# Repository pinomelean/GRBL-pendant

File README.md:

# GRBL-pendant

Hardware pendant intended for use with G-code senders for GRBL machines

### Description
The aim of this project is to produce a physical controller which functions similarly to a machine pendant, but is not limited to only that. The device would allow the user to interact with both the computer and the CNC machine without needing to reach for the mouse and keyboard for the most machining tasks.
The hardware is not limited to a single purpose, though, as the firmware can be easily changed so the controller can suit the needs of the user, and be adapted for their particular workflow.

This USB pendant Includes many buttons, encoders and a thumbstick that can be configured with the most common functions and G-code commands you need to use your machine.
It uses a Teensy++ 2 because of its physical size, IO, native USB, and ease of programming with the Arduino ecosystem, *as limited as it is*.

### Free and open source

I publish all the files necessary for anyone to "DIY" it, all files can be opened and edited with FOSS software.
Anyone with a CNC mill/router should be able to make their own if they're so inclined.

The code is written as simple as I can manage (even if I suck at it), so anyone with basic knowledge and/or an Arduino tutorial open in another tab can modify it to suit their needs.

The PCBs are designed in KiCad and made to be simple enough to be milled at home, as I've done with the first prototype.

To mill the PCBs I used, and would recommend, [Juan Pablo Caram](https://github.com/jpcaram)'s [FlatCAM](http://www.flatcam.org/) and [Martin Pittermann](https://github.com/martin2250)'s [OpenCNCPilot](https://github.com/martin2250/OpenCNCPilot)

FreeCAD was used to design the silicone keypad and the mould to cast it.
The mould and the case were milled using toolpaths generated in the path workbench.

## Pendant layout

The layout I had in mind designing this pendant, and will come by default will be the following:

The Thumbstick is used either as a mouse pointer, along with a couple of buttons for clicking, or to quickly jog the machine when pressed in.

*The Teensy can emulate a game controller thumbstick, but as not many G-code sender applications support game controllers, and those that do (I only tested UGS) may not recognize the one emulated by the teensy, the thumbstick will not be emulating a game controller for nw, and just write G-code jog commands instead. This should work with any sender.*

The buttons at the top of the pendant are dedicated to the basic machine commands: Reset, Feed hold, Cycle start/Resume at the top, and Home machine and Kill alarm lock right of the thumbstick.

There are three encoders for fine jogging of each axis. By default each detent should result in 1mm of travel, and 0.1mm if the encoder is pushed in while turning.
Pushing an encoder without turning it will zero that axis.

The two other encoders are meant for Feed and spindle speed overrides, but could be used for jogging two extra axises in a 5-axis machine if anyone's running one of those.

*I still need to figure how to send the Feed and Spindle speed override command characters through a sender application if it does not have hotkeys for that*

Next to each encoder is a button which is used to individually home that axis.
For the Feed and Spindle encoders, the button resets it to 100%.

At the bottom of the controller are the macro buttons.
The five ones in the middle are used for probing or touching against a workpiece from every direction (except from under it).

The other 4 buttons are left for any extra macros the user could need, such as turning on/off mist/flood coolant, starting/stopping the spindle, touching a bit on the tool setter...

**Of course, all of the actions are remappable and configurable to suit the needs and workflow of the user. The defaults are just what** ***I*** **think is most useful**

## Project status

- Second version built. Looks much nicer in black and white. Probably final version if no issues arise.
	- The keypad also feels nice and works very well, but the Shore A20 durometer silicone might be too soft for this application, but will do for mow.

- Keypad mould machined. Couldn't get the 3D surfacing operation to work with a ball end mill en FreeCAD, so I had to resort to Fusion360 for that operation.
	- A sprue and vent have to be drilled manually into the side to inject the silicone with a syringe and push out the air.

- First prototype mostly built, silicone keypad left to see how it all looks and feels. A couple of encoder push buttons don't work, but will do for testing.
	- Several adjustments made for a second version. Will not make a mold and keypad for the first.

- Thumbstick as mouse pointer - Done. Works pretty well in the smaller screens I use, slower in bigger ones, but it's adjustable.
- Thumbstick for jogging - UGS wouldn't recognize it in game controller mode, so It just types jogging G-code commands. Works ok.
- Encoder jogging - Works well for accurate positioning. Too slow for jogging around a bigger machine, but there's the thumbstick for that.
- Rest of the buttons - not yet programmed.

## Notes

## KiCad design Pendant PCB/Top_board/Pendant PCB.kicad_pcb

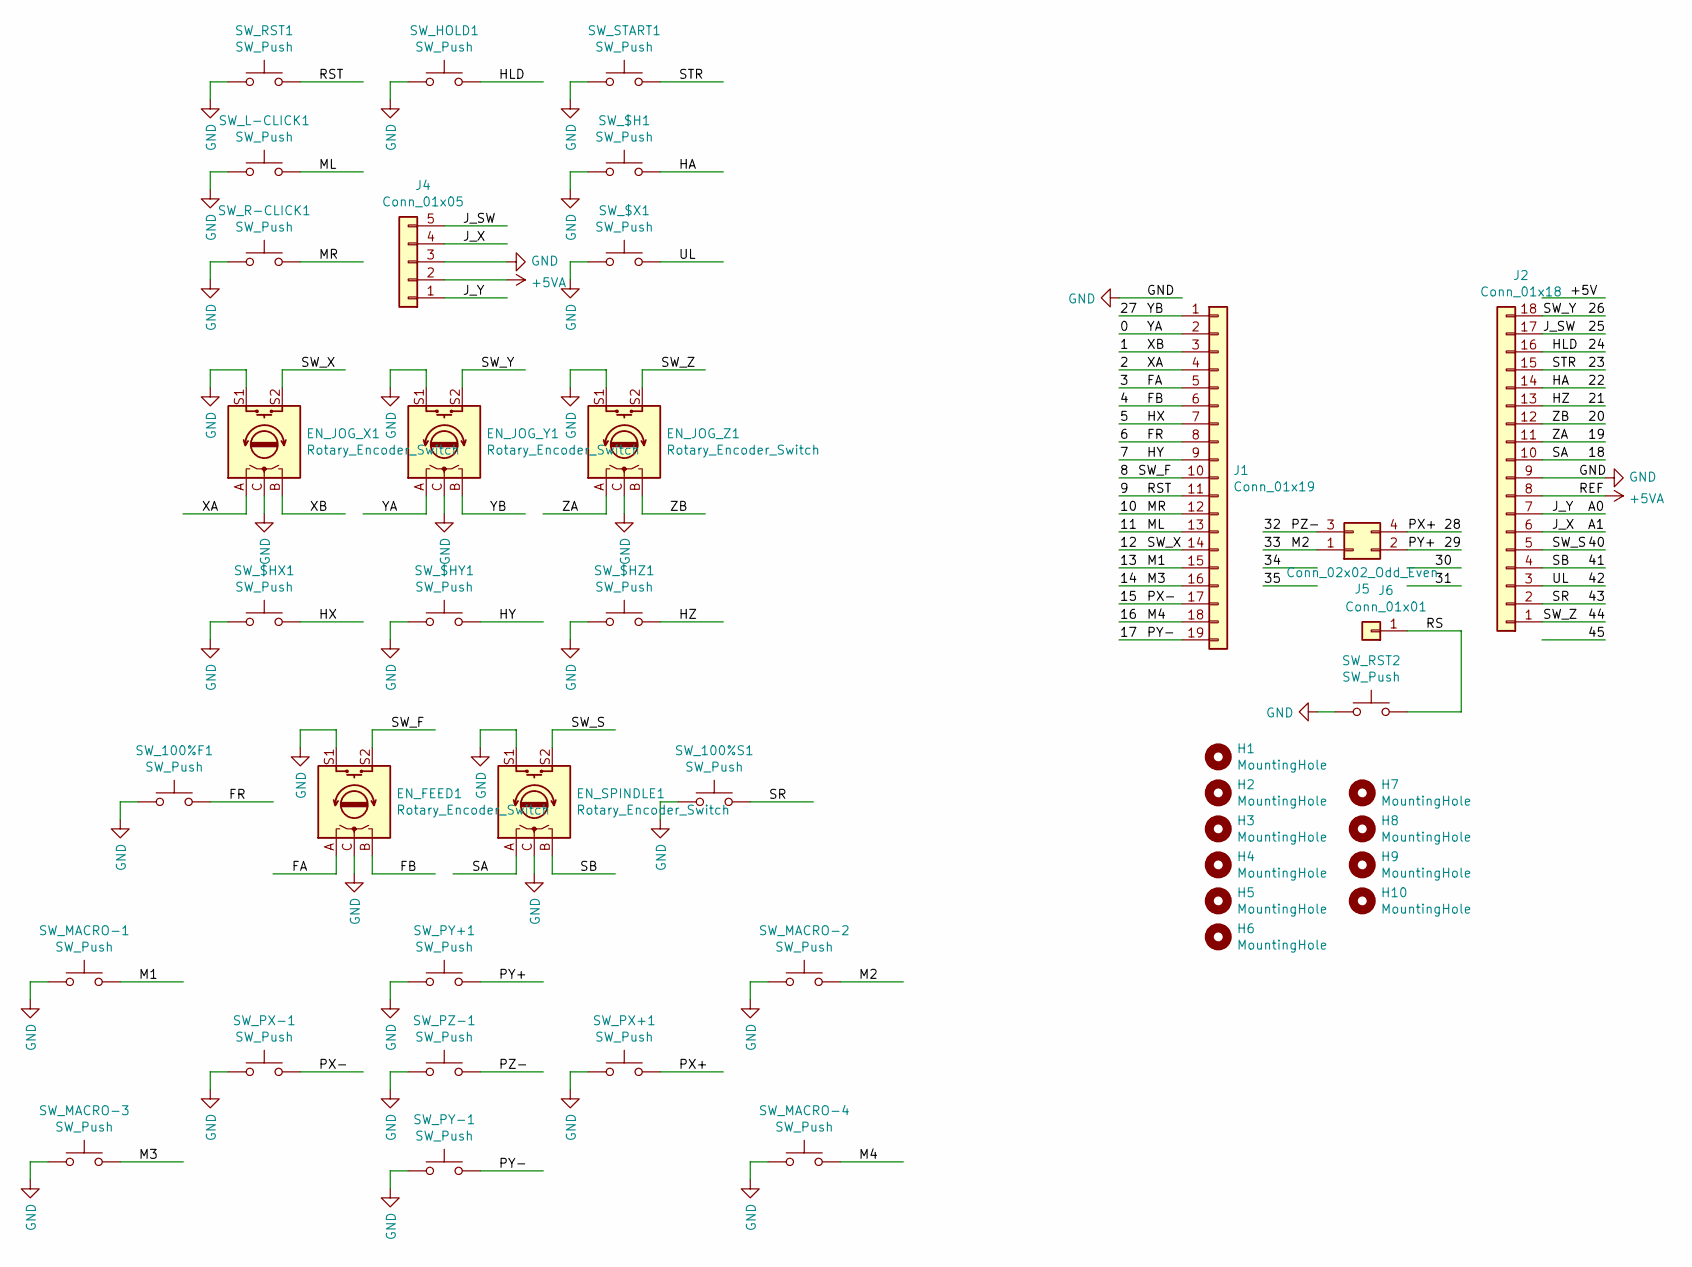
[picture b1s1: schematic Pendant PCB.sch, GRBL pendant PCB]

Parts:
EN_FEED1: Rotary_Encoder_Switch; PEC11R-4x15K
EN_JOG_X1: Rotary_Encoder_Switch; PEC11R-4x15K
EN_JOG_Y1: Rotary_Encoder_Switch; PEC11R-4x15K
EN_JOG_Z1: Rotary_Encoder_Switch; PEC11R-4x15K
EN_SPINDLE1: Rotary_Encoder_Switch; PEC11R-4x15K
H1, H2, H3, H4, H5, H6: MountingHole; MountingHole_2.5mm
H7, H8, H9, H10: MountingHole; MountingHole_3.2mm_M3
J1: Conn_01x19; PinHeader_1x19_P2.54mm_Vertical
J2: Conn_01x18; PinHeader_1x18_P2.54mm_Vertical
J4: Conn_01x05; PinHeader_1x05_P2.54mm_Vertical
J5: Conn_02x02_Odd_Even; PinHeader_2x02_P2.54mm_Vertical
J6: Conn_01x01; PinHeader_1x01_P2.54mm_Vertical
SW_100%F1, SW_100%S1: SW_Push; SW_PUSH_6mm_H7.3mm
SW_$H1: SW_Push; SW_PUSH_6mm_H7.3mm
SW_$HX1: SW_Push; SW_PUSH_6mm_H7.3mm
SW_$HY1: SW_Push; SW_PUSH_6mm_H7.3mm
SW_$HZ1: SW_Push; SW_PUSH_6mm_H7.3mm
SW_$X1: SW_Push; SW_PUSH_6mm_H7.3mm
SW_HOLD1: SW_Push; SW_PUSH_6mm_H7.3mm
SW_L-CLICK1: SW_Push; SW_PUSH_6mm_H7.3mm
SW_MACRO-1, SW_MACRO-2, SW_MACRO-3, SW_MACRO-4: SW_Push; SW_PUSH_6mm_H7.3mm
SW_PX+1: SW_Push; SW_PUSH_6mm_H7.3mm
SW_PX-1: SW_Push; SW_PUSH_6mm_H7.3mm
SW_PY+1: SW_Push; SW_PUSH_6mm_H7.3mm
SW_PY-1: SW_Push; SW_PUSH_6mm_H7.3mm
SW_PZ-1: SW_Push; SW_PUSH_6mm_H7.3mm
SW_R-CLICK1: SW_Push; SW_PUSH_6mm_H7.3mm
SW_RST1: SW_Push; SW_PUSH_6mm_H7.3mm
SW_RST2: SW_Push; SW_Tactile_SPST_Angled_PTS645Vx39-2LFS
SW_START1: SW_Push; SW_PUSH_6mm_H7.3mm

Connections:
+5VA: J2.8, J4.2
/0: EN_JOG_Y1.A, J1.2
/1: EN_JOG_X1.B, J1.3
/2: EN_JOG_X1.A, J1.4
/3: EN_FEED1.A, J1.5
/4: EN_FEED1.B, J1.6
/5: J1.7, SW_$HX1.2
/6: J1.8, SW_100%F1.2
/7: J1.9, SW_$HY1.2
/8: EN_FEED1.S2, J1.10
/9: J1.11, SW_RST1.1
/10: J1.12, SW_R-CLICK1.1
/11: J1.13, SW_L-CLICK1.1
/12: EN_JOG_X1.S2, J1.14
/13: J1.15, SW_MACRO-1.2
/14: J1.16, SW_MACRO-3.2
/15: J1.17, SW_PX-1.1
/16: J1.18, SW_MACRO-4.1
/17: J1.19, SW_PY-1.1
/18: EN_SPINDLE1.A, J2.10
/19: EN_JOG_Z1.A, J2.11
/20: EN_JOG_Z1.B, J2.12
/21: J2.13, SW_$HZ1.2
/22: J2.14, SW_$H1.1
/23: J2.15, SW_START1.1
/24: J2.16, SW_HOLD1.2
/25: J2.17, J4.5
/26: EN_JOG_Y1.S2, J2.18
/27: EN_JOG_Y1.B, J1.1
/28: J5.4, SW_PX+1.1
/29: J5.2, SW_PY+1.2
/32: J5.3, SW_PZ-1.1
/33: J5.1, SW_MACRO-2.1
/40: EN_SPINDLE1.S2, J2.5
/41: EN_SPINDLE1.B, J2.4
/42: J2.3, SW_$X1.1
/43: J2.2, SW_100%S1.2
/44: EN_JOG_Z1.S2, J2.1
/A0: J2.7, J4.1
/A1: J2.6, J4.4
/RS: J6.1, SW_RST2.2
GND: EN_FEED1.C, EN_FEED1.S1, EN_JOG_X1.C, EN_JOG_X1.S1, EN_JOG_Y1.C, EN_JOG_Y1.S1, EN_JOG_Z1.C, EN_JOG_Z1.S1, EN_SPINDLE1.C, EN_SPINDLE1.S1, J2.9, J4.3, SW_100%F1.1, SW_100%S1.1, SW_$H1.2, SW_$HX1.1, SW_$HY1.1, SW_$HZ1.1, SW_$X1.2, SW_HOLD1.1, SW_L-CLICK1.2, SW_MACRO-1.1, SW_MACRO-2.2, SW_MACRO-3.1, SW_MACRO-4.2, SW_PX+1.2, SW_PX-1.2, SW_PY+1.1, SW_PY-1.2, SW_PZ-1.2, SW_R-CLICK1.2, SW_RST1.2, SW_RST2.1, SW_START1.2

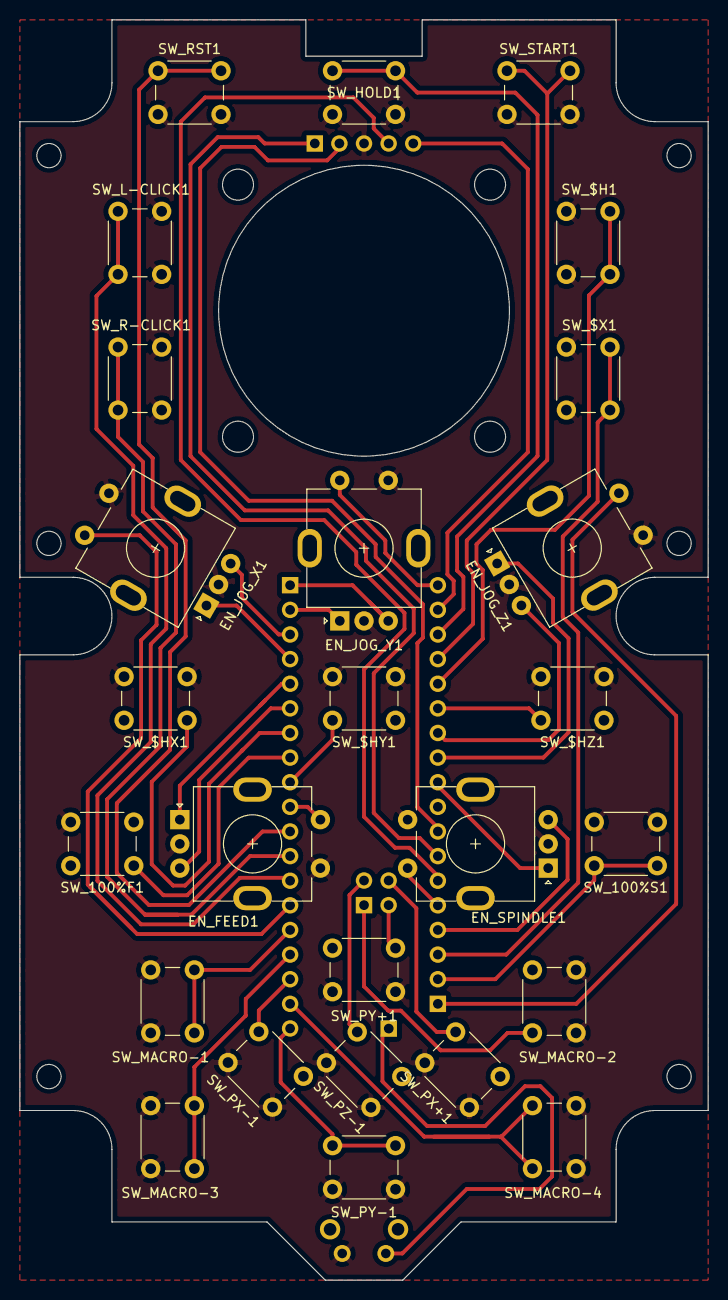
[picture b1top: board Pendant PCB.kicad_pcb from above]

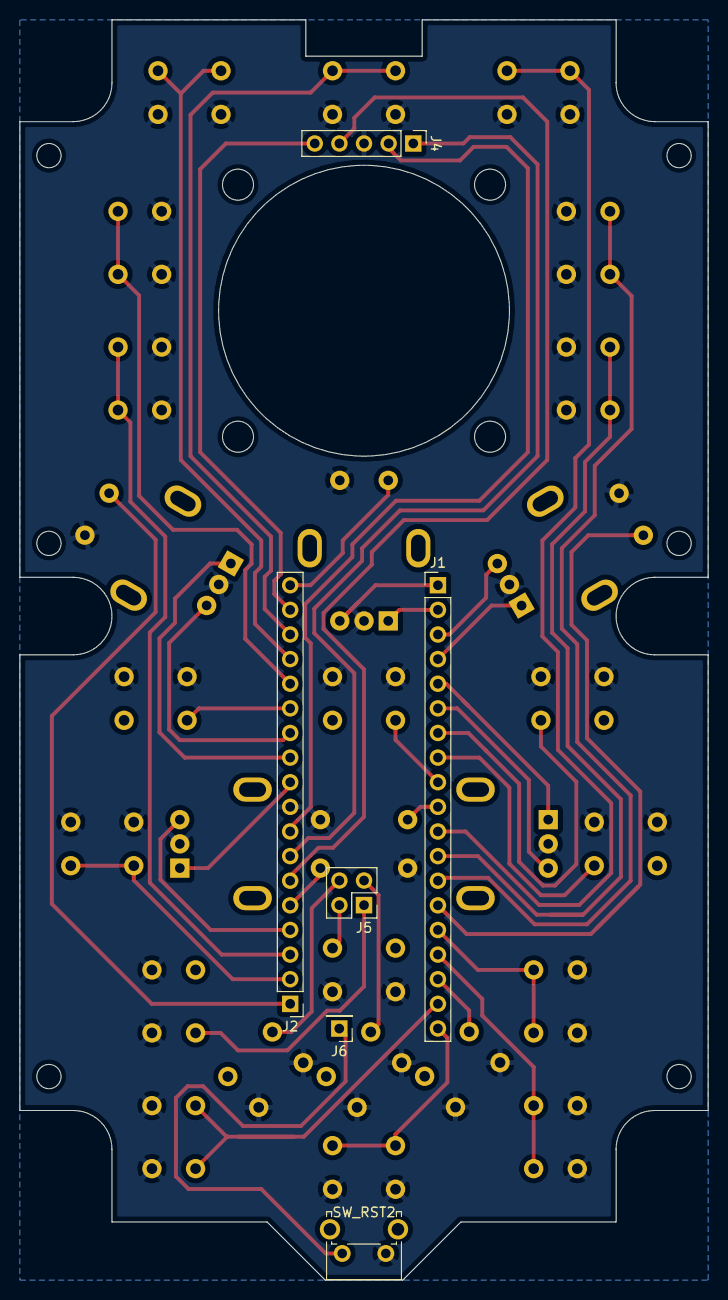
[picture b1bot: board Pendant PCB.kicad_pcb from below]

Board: 2 copper layers, 71.0 x 130.0 mm, 42 parts (6 on the bottom side), 42 nets.

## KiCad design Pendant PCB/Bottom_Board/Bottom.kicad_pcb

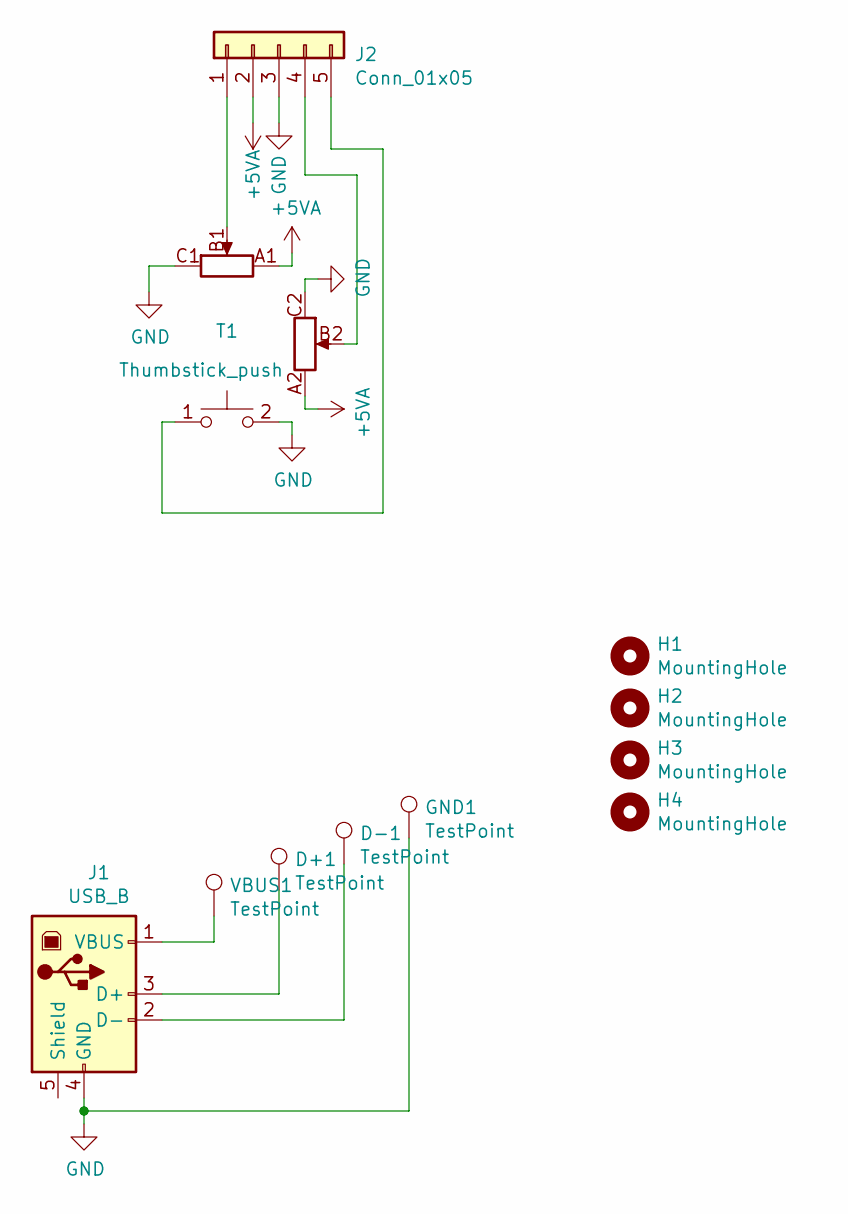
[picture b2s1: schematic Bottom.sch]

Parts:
D+1: TestPoint; TestPoint_THTPad_2.5x2.5mm_Drill1.2mm
D-1: TestPoint; TestPoint_THTPad_2.5x2.5mm_Drill1.2mm
GND1: TestPoint; TestPoint_THTPad_2.5x2.5mm_Drill1.2mm
H1, H2, H3, H4: MountingHole; MountingHole_3.2mm_M3
J1: USB_B; USB_B_Horizontal
J2: Conn_01x05; PinSocket_1x05_P2.54mm_Vertical
T1: Thumbstick_push; RKJXV1224_CAP
VBUS1: TestPoint; TestPoint_THTPad_2.5x2.5mm_Drill1.2mm

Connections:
+5VA: J2.2, T1.A1, T1.A2
GND: GND1.1, J1.4 (GND), J2.3, T1.2, T1.C1, T1.C2
unnamed: D+1.1, J1.3 (D+)
unnamed: D-1.1, J1.2 (D-)
unnamed: J1.1 (VBUS), VBUS1.1
unnamed: J2.1, T1.B1
unnamed: J2.4, T1.B2
unnamed: J2.5, T1.1

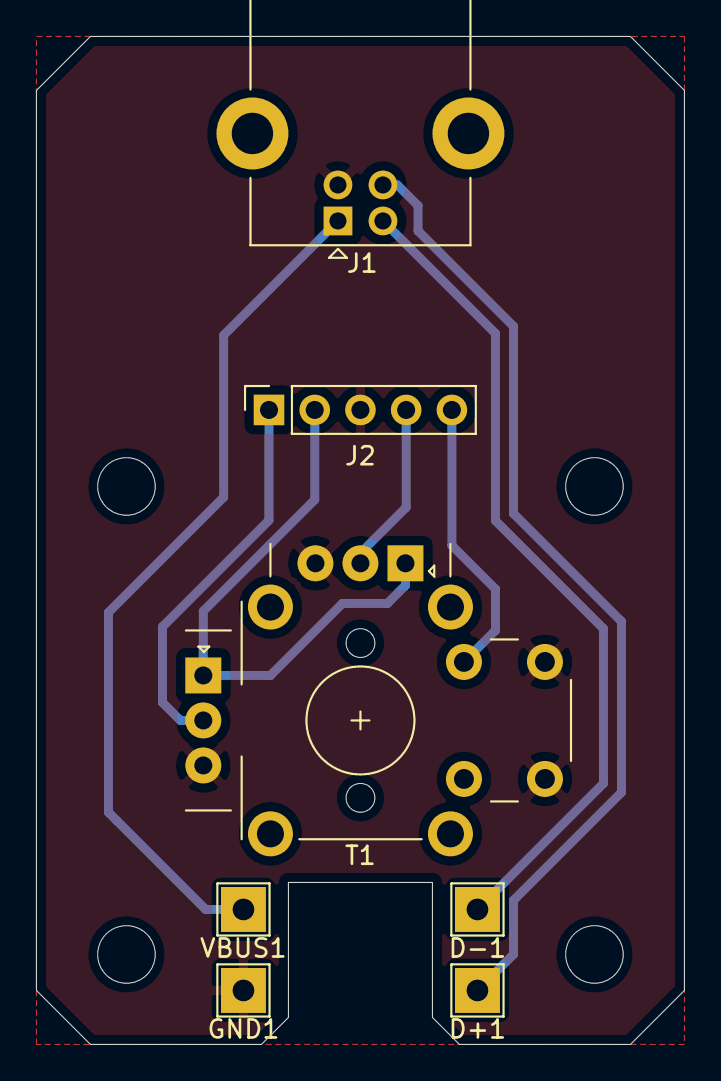
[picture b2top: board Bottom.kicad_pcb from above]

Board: 2 copper layers, 36.0 x 56.0 mm, 11 parts (0 on the bottom side), 8 nets.

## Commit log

2020-12-18 Initial code tests
2020-12-21 Added Teensy(duino) pinout for reference
2020-12-24 KiCAD project added. Layout and PCB drawings updated for cheap case
2020-12-25 Drawings updated
2020-12-26 PCB prepared. Drawings updated
2021-01-04 PCB routed. Feed and Spindle encoders moved .5mm closer to Y-axis
2021-01-06 Bottom board (Thumbstick + USB)
2021-01-07 Boards finished and revised. Fabrication outputs generated.
2021-01-09 updated cutout path
2021-01-09 Cutout as gerber for CAM processing
2021-01-13 Encoder/thumbstick jog & mouse
2021-01-14 Readme improved.
2021-01-15 Keypad 3D model and mold
2021-01-19 Changes made for 2nd version.
2021-01-28 Started keypad mold machining
2021-02-07 Second version built, fabrication files included
2021-02-07 Pinout updated
2021-02-14 Encoder Jogging completed
2021-02-15 Mouse sketch updated
2022-01-17 Brought working sub-programs together into the main "Pendant" program
